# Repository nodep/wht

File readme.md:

This project implements a 3 axis wireless gyro. The hardware consists of two parts: a tracker with sensors and a USB dongle.

The data received from the sensors can be passed to the PC through a USB dongle which enumerates as a joystick and mouse.

The tracker contains these ICs:

- Nordic Semiconductor nRF24LE1 MCU (8-bit 8051)
- InvenSense MPU-6050 (or MPU-9150) IMU (gyro and accelerometer)
- Asahi Kasei AK8975 (magnetometer)

The USB dongle uses a Nordic Semiconductor nRF24LU1+ 2.4GHz and does most of the numerical processing.

There are several variants of the tracker which vary in size and power source. The most practical variant runs off of a single AA battery and has a 3.3V boost regulator (MCP1640). Another variant uses a CR123A lithium battery without a regulator.

The tracker is designed around modules (MCU and sensors) which can be easily found on ebay or similar online shops.

The code can be compiled with sdcc (Small Device C Compiler) and flashed to the Nordic nRF chips using nrfburn: https://github.com/nodep/nrfburn

The project contains design files (OpenSCAD and stl) for 3D printed enclosures for the tracker and the dongle.

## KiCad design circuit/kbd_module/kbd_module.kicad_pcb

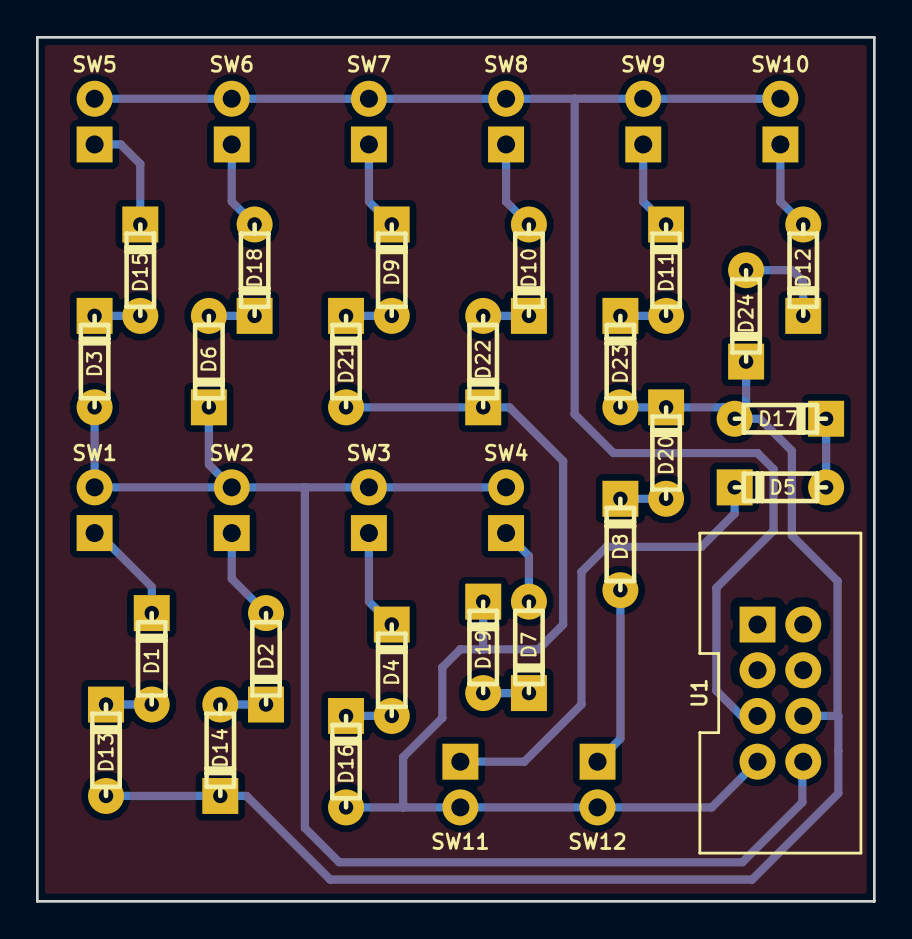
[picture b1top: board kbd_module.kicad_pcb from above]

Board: 2 copper layers, 46.5 x 48.0 mm, 37 parts (0 on the bottom side), 28 nets.

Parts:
D1, D2, D3, D4, D5, D6, D7, D8, D9, D10, D11, D12, D13, D14, D15, D16, D17, D18, D19, D20, D21, D22, D23, D24: 1n4148; SOD27_RM5_5
SW1, SW2, SW3, SW4, SW5, SW6, SW7, SW8, SW9, SW10, SW11, SW12: SW_SIMPLE; ExtSwitch
U1: NRF24LE1_PROG; NRF_ICSP_RibbonCable

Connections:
/FCSN: D3.2, D6.1, SW1.2, SW2.2, SW3.2, SW4.2, U1.8
/FMISO: D16.2, D19.1, D21.2, D22.1, SW11.2, SW12.2, U1.7
/FMOSI: D13.2, D14.1, D17.2, D20.1, D23.2, D24.1, U1.6
/FSCK: SW5.2, SW6.2, SW7.2, SW8.2, SW9.2, SW10.2, U1.5
unnamed: D1.1, SW1.1
unnamed: D1.2, D13.1
unnamed: D2.2, SW2.1
unnamed: D4.1, SW3.1
unnamed: D5.1, SW11.1
unnamed: D7.2, SW4.1
unnamed: D8.2, SW12.1
unnamed: D9.1, SW7.1
unnamed: D10.1, D22.2
unnamed: D10.2, SW8.1
unnamed: D11.1, SW9.1
unnamed: D11.2, D23.1
unnamed: D12.1, D24.2
unnamed: D12.2, SW10.1
unnamed: D2.1, D14.2
unnamed: D15.1, SW5.1
unnamed: D3.1, D15.2
unnamed: D4.2, D16.1
unnamed: D5.2, D17.1
unnamed: D6.2, D18.1
unnamed: D18.2, SW6.1
unnamed: D7.1, D19.2
unnamed: D8.1, D20.2
unnamed: D9.2, D21.1

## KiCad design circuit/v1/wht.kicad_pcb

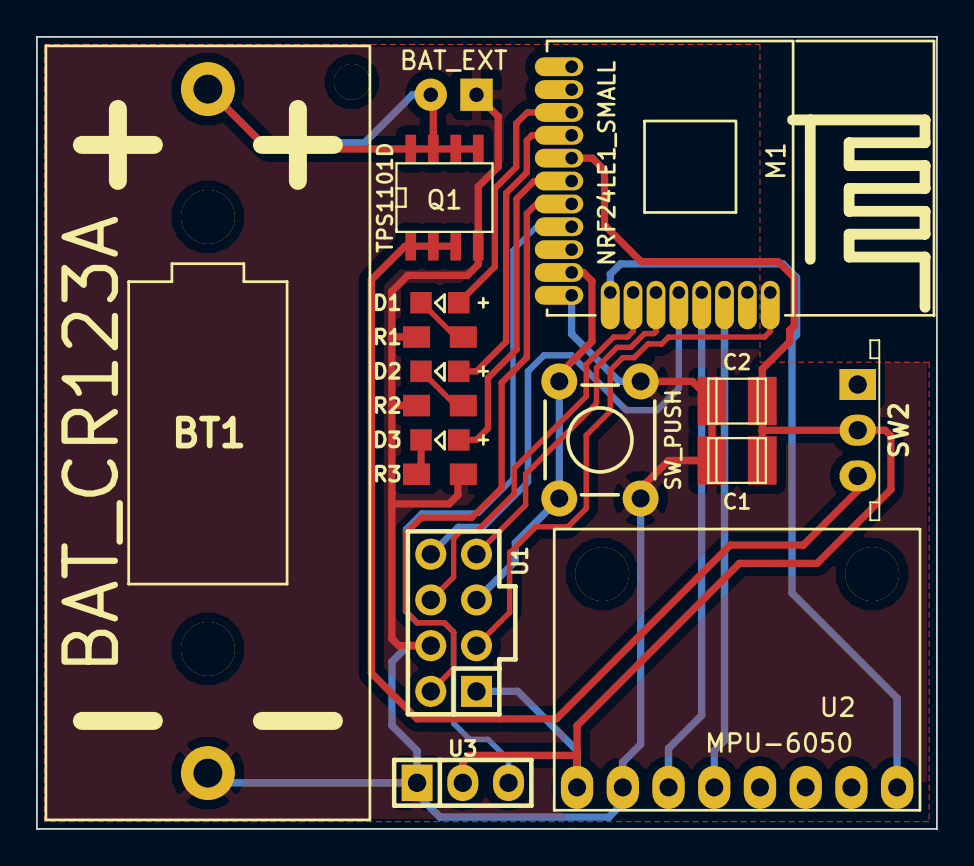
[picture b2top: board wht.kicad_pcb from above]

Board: 2 copper layers, 50.0 x 44.0 mm, 17 parts (0 on the bottom side), 20 nets.

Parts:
BT1: BAT_CR123A; CR123
BT2: BAT_EXT; BATTERY_EXT
C1: C; c_1210
C2: CP1; c_1210
D1, D2, D3: LED; LED-0805
M1: NRF24LE1_SMALL
Q1: TPS1101D; SOIC-8_N
R1, R2, R3: R; Resistor_SMD0805_HandSoldering
SW1: SW_PUSH; TACTILE-PTH
SW2: SWITCH_INV; ESP2010_switch
U1: NRF24LE1_PROG; Pin_Header_Straight_2x04
U2: MPU-6050; MPU6050
U3: UART; Pin_Header_Straight_1x03

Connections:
/FCSN: M1.15, U1.8
/FMISO: M1.14, U1.7
/FMOSI: M1.13, U1.6
/FSCK: M1.10, SW1.1, U1.5
/PROG: M1.7, U1.2
/RESET: M1.19, U1.3
/SCL: M1.16, U2.3
/SDA: M1.17, U2.4
GND: BT1.2, BT2.2, C1.2, C2.2, M1.11, Q1.4, R1.1, R2.1, R3.1, SW1.2, U1.4, U2.2, U3.1
unnamed: BT1.1, BT2.1, Q1.5, Q1.6, Q1.7, Q1.8
unnamed: D1.1, M1.3
unnamed: D1.2, R1.2
unnamed: D2.1, M1.4
unnamed: D2.2, R2.2
unnamed: D3.1, M1.6
unnamed: D3.2, R3.2
unnamed: M1.8, U3.3
unnamed: M1.12, U2.8
unnamed: Q1.1, Q1.2, Q1.3, SW2.3
VCC: C1.1, C2.1, M1.5, SW2.2, U1.1, U2.1, U3.2

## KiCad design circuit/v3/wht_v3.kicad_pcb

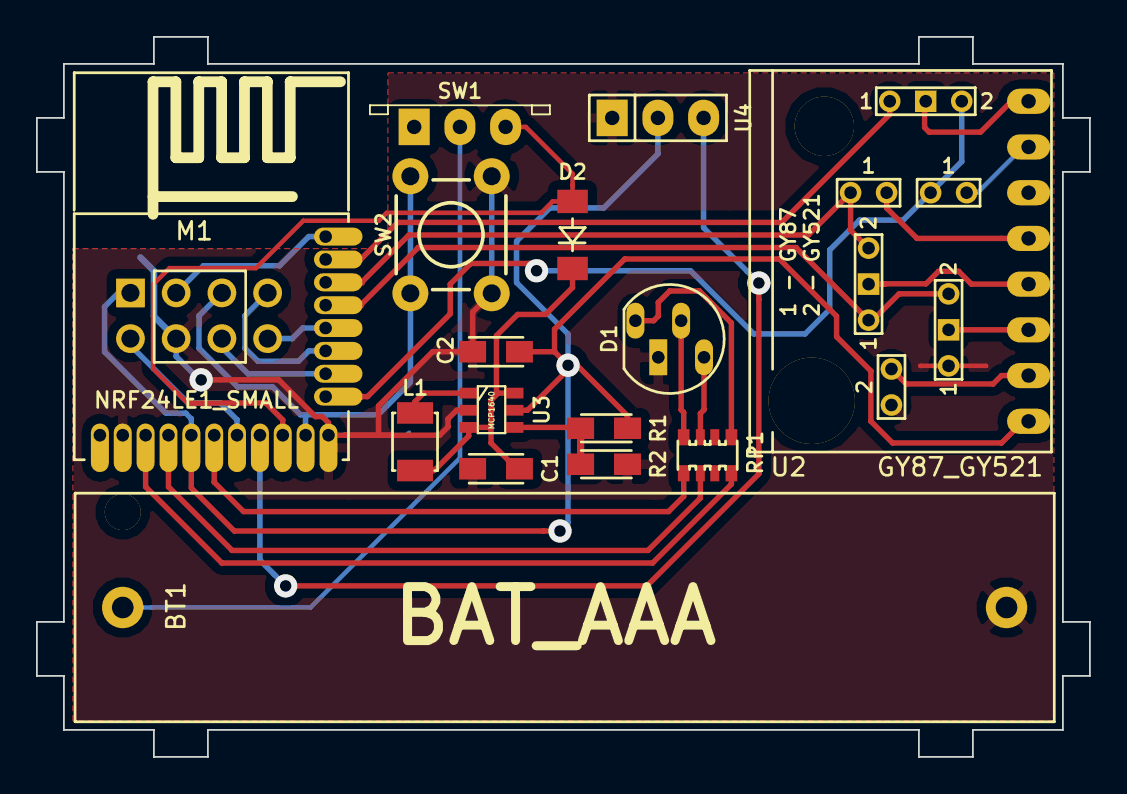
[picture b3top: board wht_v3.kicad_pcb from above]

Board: 2 copper layers, 58.5 x 40.0 mm, 22 parts (1 on the bottom side), 30 nets.

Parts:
BT1: BAT_AAA; BATT_HOLDER_AAAx1_KEYSTONE_1021
C1: 4.7uF; Capacitor_SMD0805_HandSoldering
C2: 10uF; Capacitor_SMD0805_HandSoldering
D1: LED_RGB_CC
D2: DIODESCH; Diode-MiniMELF_Handsoldering
JP1, JP2: 1; JumperTHT
JP3: 2; JumperTHT
L1: 4.7uH; INDUCTOR_NLCV25T
M1: NRF24LE1_SMALL
R1: 511K; Resistor_SMD0805_HandSoldering
R2: 348K; Resistor_SMD0805_HandSoldering
RP1: R_PACK4; Resistor_Array_x4_1206
SL1, SL3: SEL_P4; SelectTHT
SL2: SEL_P3; SelectTHT
SW1: SWITCH_INV; ESP2010_switch
SW2: SW_PUSH; TACTILE-PTH
U1: NRF24LE1_PROG; NRF_ICSP_PogoPinsHoles
U2: GY87_GY521
U3: MCP1640; SOT23_6_WHT
U4: DBG_CONN; Pin_Header_Straight_1x03

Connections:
/DRDY: M1.18, SL3.1
/FCSN: M1.15, U1.8
/FMISO: M1.14, U1.7
/FMOSI: M1.13, U1.6
/FSCK: M1.10, SW2.1, U1.5
/GR: M1.6, RP1.1
/INT: JP1.1, M1.12, SL3.3
/PROG: M1.7, U1.2
/RD: M1.3, RP1.4
/RESET: M1.19, U1.3
/SCL: M1.16, SL1.1, SL2.3
/SDA: JP2.1, M1.17, SL1.3
/TXD: M1.8, U4.3
/VBATT: D2.1, M1.9, SW1.3
/YL: M1.4, RP1.2
GND: BT1.2, C1.2, C2.2, D1.CC, JP3.1, M1.2, M1.11, R2.1, SL2.1, SW2.2, U1.4, U3.2, U4.1
unnamed: BT1.1, SW1.2
unnamed: C1.1, D2.2, L1.1, U3.3, U3.6
unnamed: D1.BA, RP1.7
unnamed: D1.GA, RP1.8
unnamed: D1.RA, RP1.5
unnamed: JP1.2, U2.7
unnamed: JP2.2, U2.5
unnamed: JP3.2, U2.2
unnamed: L1.2, U3.1
unnamed: R1.2, R2.2, U3.4
unnamed: SL1.2, U2.4
unnamed: SL2.2, U2.3
unnamed: SL3.2, U2.8
VCC: C2.1, M1.5, R1.1, U1.1, U2.1, U3.5, U4.2

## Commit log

2016-09-17 image link
2016-09-17 enclosures
2016-09-17 typos
2016-10-29 forgot the tracker source :(
2016-11-01 the first mouse buttons
2016-11-01 kbd_module diode correction
2016-11-02 dual diodes
2016-11-06 moved the diodes from the edge
2016-11-07 added license
2016-11-07 addeed empty objs folders
2016-11-11 removed mouse buttons from the dongle code
2016-11-13 moved the buttons to the joystick report
2016-12-06 fixed the DBG_MODE and KBD_MODULE bug
2016-12-20 1.3d version (keyboard module)
